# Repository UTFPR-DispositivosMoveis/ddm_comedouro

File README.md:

# ddm_comedouro

1. Aplicativo

2. Raspbarry

3. InLoco - MSP430G...

> Projeto desenvolvido na Materia de Desenvolvimento De Aplicativos para Dispositvos Moveis - 8CP.

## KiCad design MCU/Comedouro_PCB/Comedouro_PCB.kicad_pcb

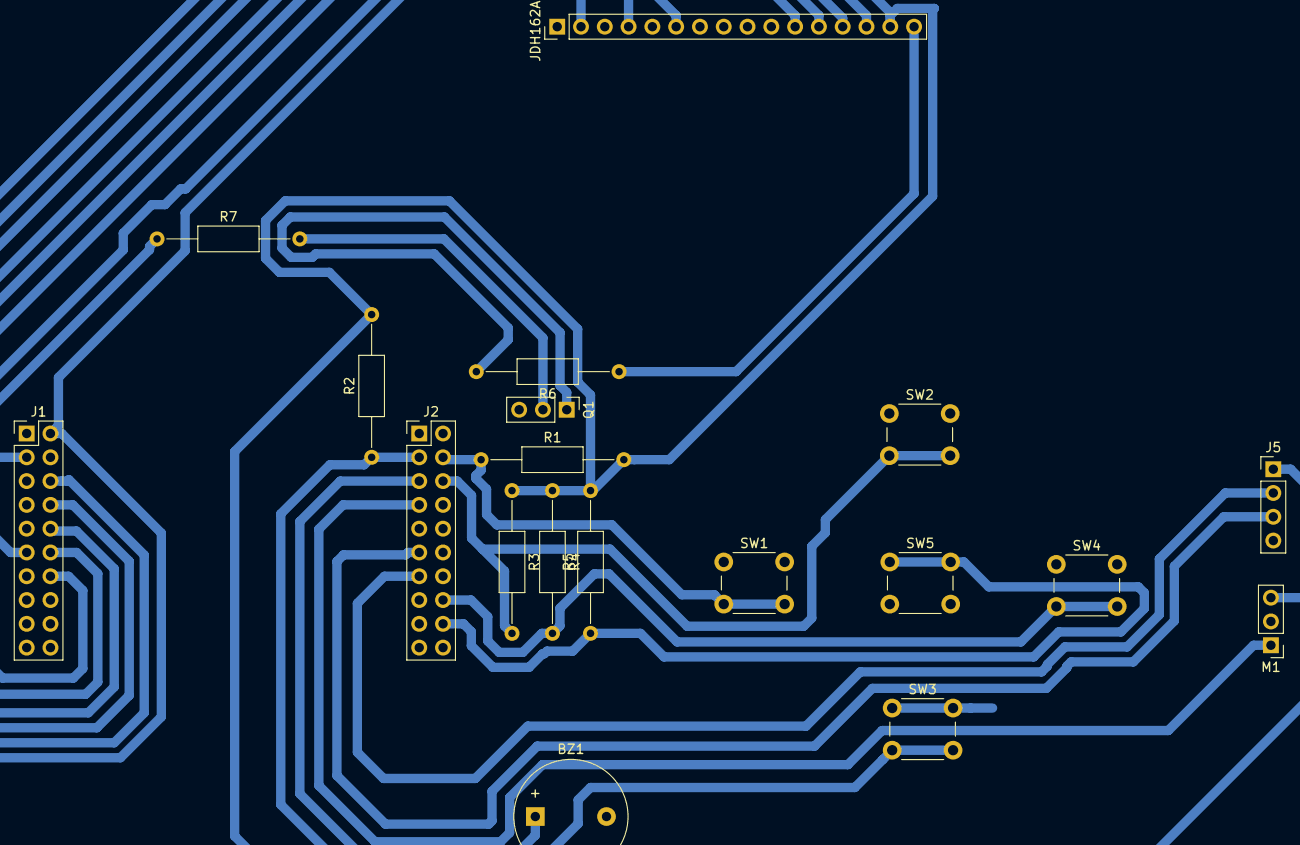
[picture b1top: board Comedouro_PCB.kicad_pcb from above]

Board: 2 copper layers, 19 parts (0 on the bottom side), 21 nets.

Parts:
BZ1: Buzzer; Buzzer_12x9.5RM7.6
J1, J2: Conn_02x10_Odd_Even; PinHeader_2x10_P2.54mm_Vertical
J5: HC-SR04; PinHeader_1x04_P2.54mm_Vertical
JDH162A1: LCD JDH162A; PinHeader_1x16_P2.54mm_Vertical
M1: Motor_Servo; PinHeader_1x03_P2.54mm_Vertical
Q1: Q_NPN_CBE; PinHeader_1x03_P2.54mm_Vertical
R1, R2, R3, R4, R5, R6, R7: R; R_Axial_DIN0207_L6.3mm_D2.5mm_P15.24mm_Horizontal
SW1, SW2, SW3, SW4, SW5: SW_Push; SW_PUSH_6mm

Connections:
+5V: J1.2, J5.1, JDH162A1.2, JDH162A1.15, M1.3, R1.2, R2.2, R3.1, R4.1, R5.2
GNDPWR: BZ1.2, J1.4, J2.2, J5.4, JDH162A1.1, JDH162A1.3, JDH162A1.5, M1.2, Q1.3, SW1.1, SW2.1, SW3.1, SW4.1, SW5.2
unnamed: BZ1.1, J2.5
unnamed: J1.3, R7.1
unnamed: J1.6, JDH162A1.14
unnamed: J1.8, JDH162A1.13
unnamed: J1.10, JDH162A1.12
unnamed: J1.11, JDH162A1.4
unnamed: J1.12, JDH162A1.11
unnamed: J1.14, JDH162A1.6
unnamed: J2.3, R2.1, SW3.2
unnamed: J2.4, R1.1, SW1.2
unnamed: J2.6, R3.2, SW2.2
unnamed: J2.7, M1.1
unnamed: J2.11, J5.3
unnamed: J2.13, J5.2
unnamed: J2.16, R4.2, SW4.2
unnamed: J2.18, R5.1, SW5.1
unnamed: JDH162A1.16, R6.1
unnamed: Q1.1, R6.2
unnamed: Q1.2, R7.2

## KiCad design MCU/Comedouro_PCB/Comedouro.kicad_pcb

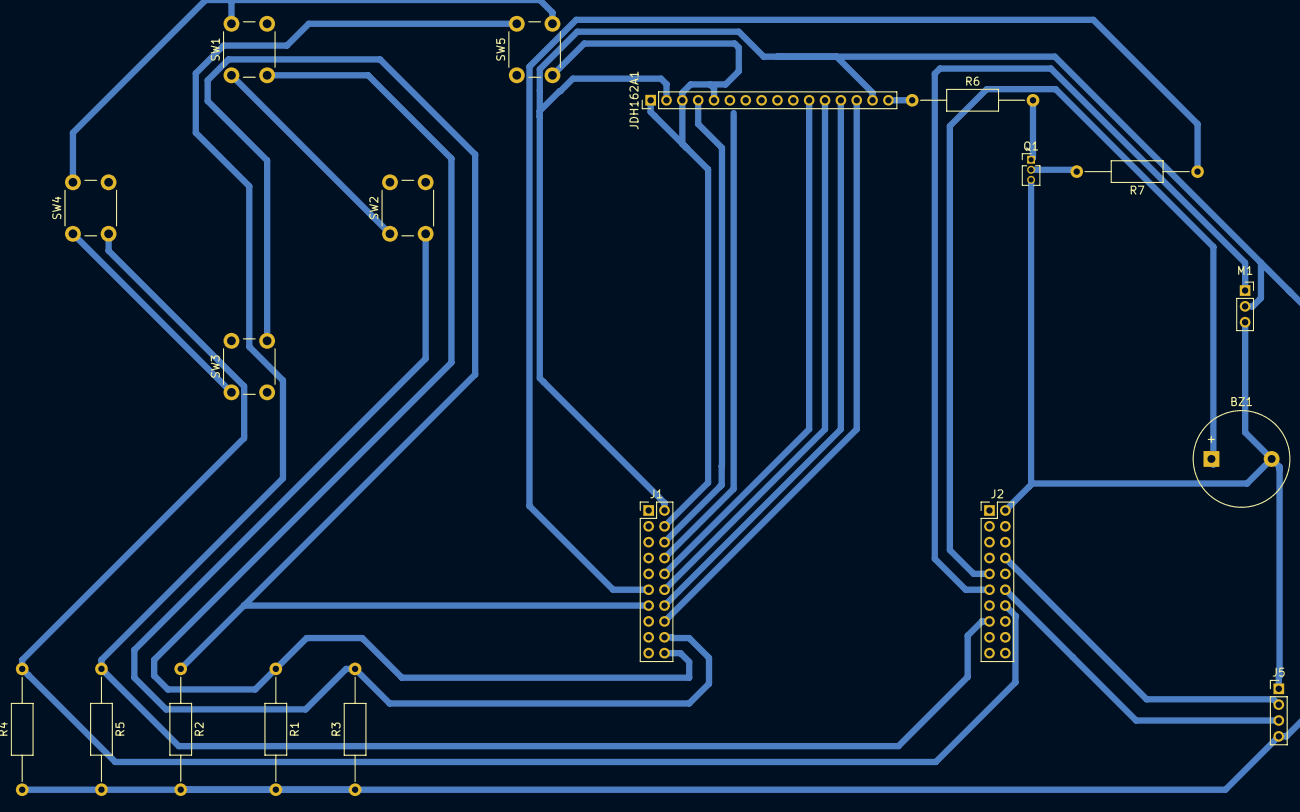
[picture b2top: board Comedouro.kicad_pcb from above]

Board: 2 copper layers, 19 parts (0 on the bottom side), 21 nets.

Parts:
BZ1: Buzzer; Buzzer_12x9.5RM7.6
J1, J2: Conn_02x10_Odd_Even; PinHeader_2x10_P2.00mm_Vertical
J5: HC-SR04; PinHeader_1x04_P2.00mm_Vertical
JDH162A1: LCD JDH162A; PinHeader_1x16_P2.00mm_Vertical
M1: Motor_Servo; PinSocket_1x03_P2.00mm_Vertical
Q1: Q_NPN_CBE; PinHeader_1x03_P1.27mm_Vertical
R1, R2, R3, R4, R5, R6, R7: R; R_Axial_DIN0207_L6.3mm_D2.5mm_P15.24mm_Horizontal
SW1, SW2, SW3, SW4, SW5: SW_Push; SW_PUSH_6mm

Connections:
+5V: J1.2, J5.4, JDH162A1.2, JDH162A1.15, M1.2, R1.2, R2.2, R3.1, R4.1, R5.2
GNDPWR: BZ1.2, J1.4, J2.2, J5.1, JDH162A1.1, JDH162A1.3, JDH162A1.5, M1.3, Q1.3, SW1.1, SW2.1, SW3.1, SW4.1, SW5.2
unnamed: BZ1.1, J2.9
unnamed: J1.6, JDH162A1.4
unnamed: J1.8, JDH162A1.6
unnamed: J1.10, JDH162A1.11
unnamed: J1.11, R7.1
unnamed: J1.12, JDH162A1.12
unnamed: J1.13, R2.1, SW3.2
unnamed: J1.14, JDH162A1.13
unnamed: J1.16, JDH162A1.14
unnamed: J1.18, R3.2, SW2.2
unnamed: J1.20, R1.1, SW1.2
unnamed: J2.8, J5.2
unnamed: J2.11, M1.1
unnamed: J2.12, J5.3
unnamed: J2.14, R4.2, SW4.2
unnamed: J2.15, R5.1, SW5.1
unnamed: JDH162A1.16, R6.1
unnamed: Q1.1, R6.2
unnamed: Q1.2, R7.2

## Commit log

2018-09-04 Set theme jekyll-theme-minimal
2018-09-05 Add pasta middle
2018-09-10 Adicionando a base do APP mais a base do servidor
2018-09-10 Adicionado pequeno teste de servidor com socket TCP e threads, ta meio merda mas funciona
2018-09-12 Adicionando arquivos MCU
2018-09-12 testando
2018-09-12 testando2
2018-09-12 Adicionando biblioteca 44780.h p/ msp430
2018-09-12 aula dia 12 de setembro, melhorias de conexao que não funcionam
2018-09-12 Essa merda volto pro do fav, coisa porca
2018-09-12 ta ai
2018-09-17 Aquela mexida pq to intediado
2018-09-17 ATUALIZADA ESSA MERDA AQUI AO SOM DE METALLICA \m/
2018-09-17 BaseApp: Adicionando campus para digitar IP e separando métodos.
    BaseApp/.../app/.../testesock/ClientTCP.java: Agora o método construtor da
    classe abre a conexão com o servidor, o ClientSendReq envia uma requisicao para
    o servidor e como resposta recebe uma string. Essa string será utilizada no
    decorrer do AP, ou somente como confirmação.
    BaseApp/../app/.../testesock/MainActivity.java: Classe RunClient deve esta em
    outro arquivo. Nela sera enviada a requisicao para o cliente e a sua resposta
2018-09-17 BaseApp: Criando um arquivo para a classe RunClient exclusiva.
    TesteSock/.../java/.../testesock/RunClient.java: Classe intermediaria na qual
    será responsável por chamar a classe responsável para enviar os dados pelo o
    Socket. Essa classe irá receber a resposta de requisição e deverá chamar um
    callback da UI para poder fazer as devidas alterações, mostrando elas para o
    usuário.
    TesteSock/.../java/.../testesock/MainActivity.java: Excluindo a classse
2018-09-19 server.c - Adicionado a separação da string de comunicação de sockets, aguardo de definição das funções e parâmetros aceitos
2018-09-19 BaseApp: adicionando tela de configuração de hora Alterado a formado das transições das janelas e atualização dos campos de texto. Criada nova janela para modo manual. Campos de hora padronizados.
2018-09-20 server.c Identificando quando for função get e set TODO - Necessário implementar a funcionalidade de UART
2018-09-20 Alguma coisa no BaseApp
2018-09-20 Adicionando biblioteca LCD, para MSP430\n É preciso adaptar essa biblioteca
2018-09-21 display rodando com dois botoes - falta maquina de estados
2018-09-22 maquina de estados funcionando - ainda tem bugs no display ao incrementar as variaveis
2018-09-24 aqruivos do display organizados em uma pasta
2018-09-24 Adicionando interface entre a tela e o socket
2018-09-24 Teste
2018-09-24 Removendo alguma coisa
2018-09-24 reste
2018-09-24 uart.c : Funcionamento básico da comunicação UART entre rasp e MSP
2018-09-25 Display OK
2018-09-26 Middle/uart.c : Deixou de existir pois só era um mero teste nesta vida; Middle/server.c: Implementadas as threads de send e receive da uart; TODO: complementar as funções da uart;
    define_params.txt: Funções para a comunicação;
2018-09-29 incluida variavel de tempo aberto no display
2018-10-01 Middle/server.c: Iniciado esquema salvar em arquivo; Em desenvolvimento a interação socket/uart;
2018-10-02 Middle/serial.c: Adicionado para demonstrar o funcionamendo da serial;
2018-10-02 PCB versão 1
2018-10-03 PCB versão 2
2018-10-03 PCB versão 3 e HD44780 com port
2018-10-03 # WARNING: head commit changed in the meantime
    incluido variavel de tempo aberto no display
2018-10-04 commit pro shomuzaka usar
2018-10-04 motor+buzzer+ultrassom em um bloco único
2018-10-04 Adicionado padrão de comunicação entre app-rasp-uart
2018-10-05 Middle/configs.save: Criado arquivo para salvar parâmetros de configuração Middle/file_man.c: Arquivo para gerenciamento dos arquivos de parametros Middle/socket.c: Arquivo de conexao entre app e rasp
    TODO: Juntar tudo
2018-10-06 Interface alpha concluída
2018-10-06 Atualizando TestSock
2018-10-06 limpando as imundice do código do motor (1)
2018-10-06 Adicionando comunicacao com o sock
2018-10-07 limpando as imundice do código do motor (2) --Fazer o parser genérico em C --Terminar de organizar o IO
2018-10-08 limpando as imundice do código do motor (3) --Fazer o parser genérico em C --Fazer a regra de 3 pro motor --Configurar o RTC
2018-10-08 tudo feito na interrupção da RTC --testar as funções antes de usar --do jeito que está deve gerar uma interrupção por minuto
2018-10-09 Middle/server.c Juntando as partes no server.c
2018-10-13 Display mostrando minutos
2018-10-13 + Display mostrando minutos (falta testar) e setando o tempo do motor em millisegundos
    + Global_Var.h com as variaveis externas que serão mostradas
    - Bug no timer quando tenta usar o motor e o sensor juntos
2018-10-17 Middle/server.c : +fucionamento de enviar dados por uart, e o quase todo o parse. TODO: Acesso e controle do aquivo, receber dados da uart de parametros atualizados
2018-10-17 aaaaaa
2018-10-17 Adicionando comunicao Manual
2018-10-17 problema do timer OK (testar)
2018-10-21 Vai budega
2018-10-24 Ajeitando configuracoes
2018-10-24 Atualizado padrão de comunicação UART
2018-10-24 o mesmo de antes
2018-10-24 Display funcionando com periféricos - Bug: display liga por conta na interrupção do RTC
2018-10-24 Não testado servidor mas em teoria está tudo ok
2018-10-27 Acho que funcionando o server
2018-10-30 Middle/server.py: Se precisar um servidor em python
2018-10-31 Uart
2018-11-05 safsadsfa
2018-11-05 Create logo to app and apply in app
2018-11-07 Criada pasta dos esquemas de impressão 3d
2018-11-12 bugo tudo não sei se funciona
2018-11-14 deu bom
2018-11-22 ADicionadas as impressões da tela LCD, teclado e da tampa
2018-12-05 Iniciando os alarmes em horários default
2018-12-10 Ajeitando todas as paradinhas
2018-12-10 bug na máquina de estados arrumado
2018-12-11 Fix bugs in app
2018-12-12 last commit
2018-12-20 Retoques finais
